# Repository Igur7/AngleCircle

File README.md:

# AngleCircle — czterowarstwowa płytka PCB do lokalizacji dźwięku

**AngleCircle** to projekt **okrągłej, czterowarstwowej płytki PCB**, opracowywanej w **KiCadzie** do systemu lokalizacji kierunku źródła dźwięku. System wykorzystuje **ESP32-S3** i **cztery cyfrowe mikrofony MEMS I²S**, rozmieszczone wokół płytki.

Celem projektu jest integracja elektroniki, zasilania i czujników w jednym module oraz ograniczenie problemów z połączeniami przewodowymi, które występowały na etapie prototypowania.

## Założenia projektowe

- Okrągła geometria płytki dostosowana do układu czterech mikrofonów.
- **Cztery warstwy miedzi** umożliwiające rozdzielenie sygnałów, zasilania oraz pól masy.
- Projektowanie ciągłych ścieżek prądu powrotnego i odpowiedniego połączenia obszarów GND za pomocą przelotek.
- Prowadzenie linii **I²S** (BCLK, WS/LRCLK i DATA) z uwzględnieniem integralności sygnałów i geometrii połączeń.
- Integracja z mikrokontrolerem **ESP32-S3** oraz elementami elektroniki pomocniczej.
- Przygotowanie schematu i layoutu PCB w **KiCadzie**.

## Architektura mikrofonów

Cztery mikrofony tworzą dwie pary pomiarowe, używane do estymacji opóźnienia nadejścia dźwięku (**TDOA**):

```text
         GÓRA

  MIC 1          MIC 2
 (lewy górny)  (prawy górny)
       \        /
        \      /
         \    /
          \  /
           \/
           /\
          /  \
         /    \
        /      \
       /        \
  MIC 3          MIC 4
 (lewy dolny) (prawy dolny)

         DÓŁ

 I²S1: MIC 1 + MIC 4
 I²S0: MIC 2 + MIC 3
```

Przyjęta w firmware koncepcja pomiaru łączy mikrofony w **dwie przekątne**. Każda przekątna jest obsługiwana przez oddzielny kontroler I²S, aby zapewnić synchronizację wewnątrz pary pomiarowej.

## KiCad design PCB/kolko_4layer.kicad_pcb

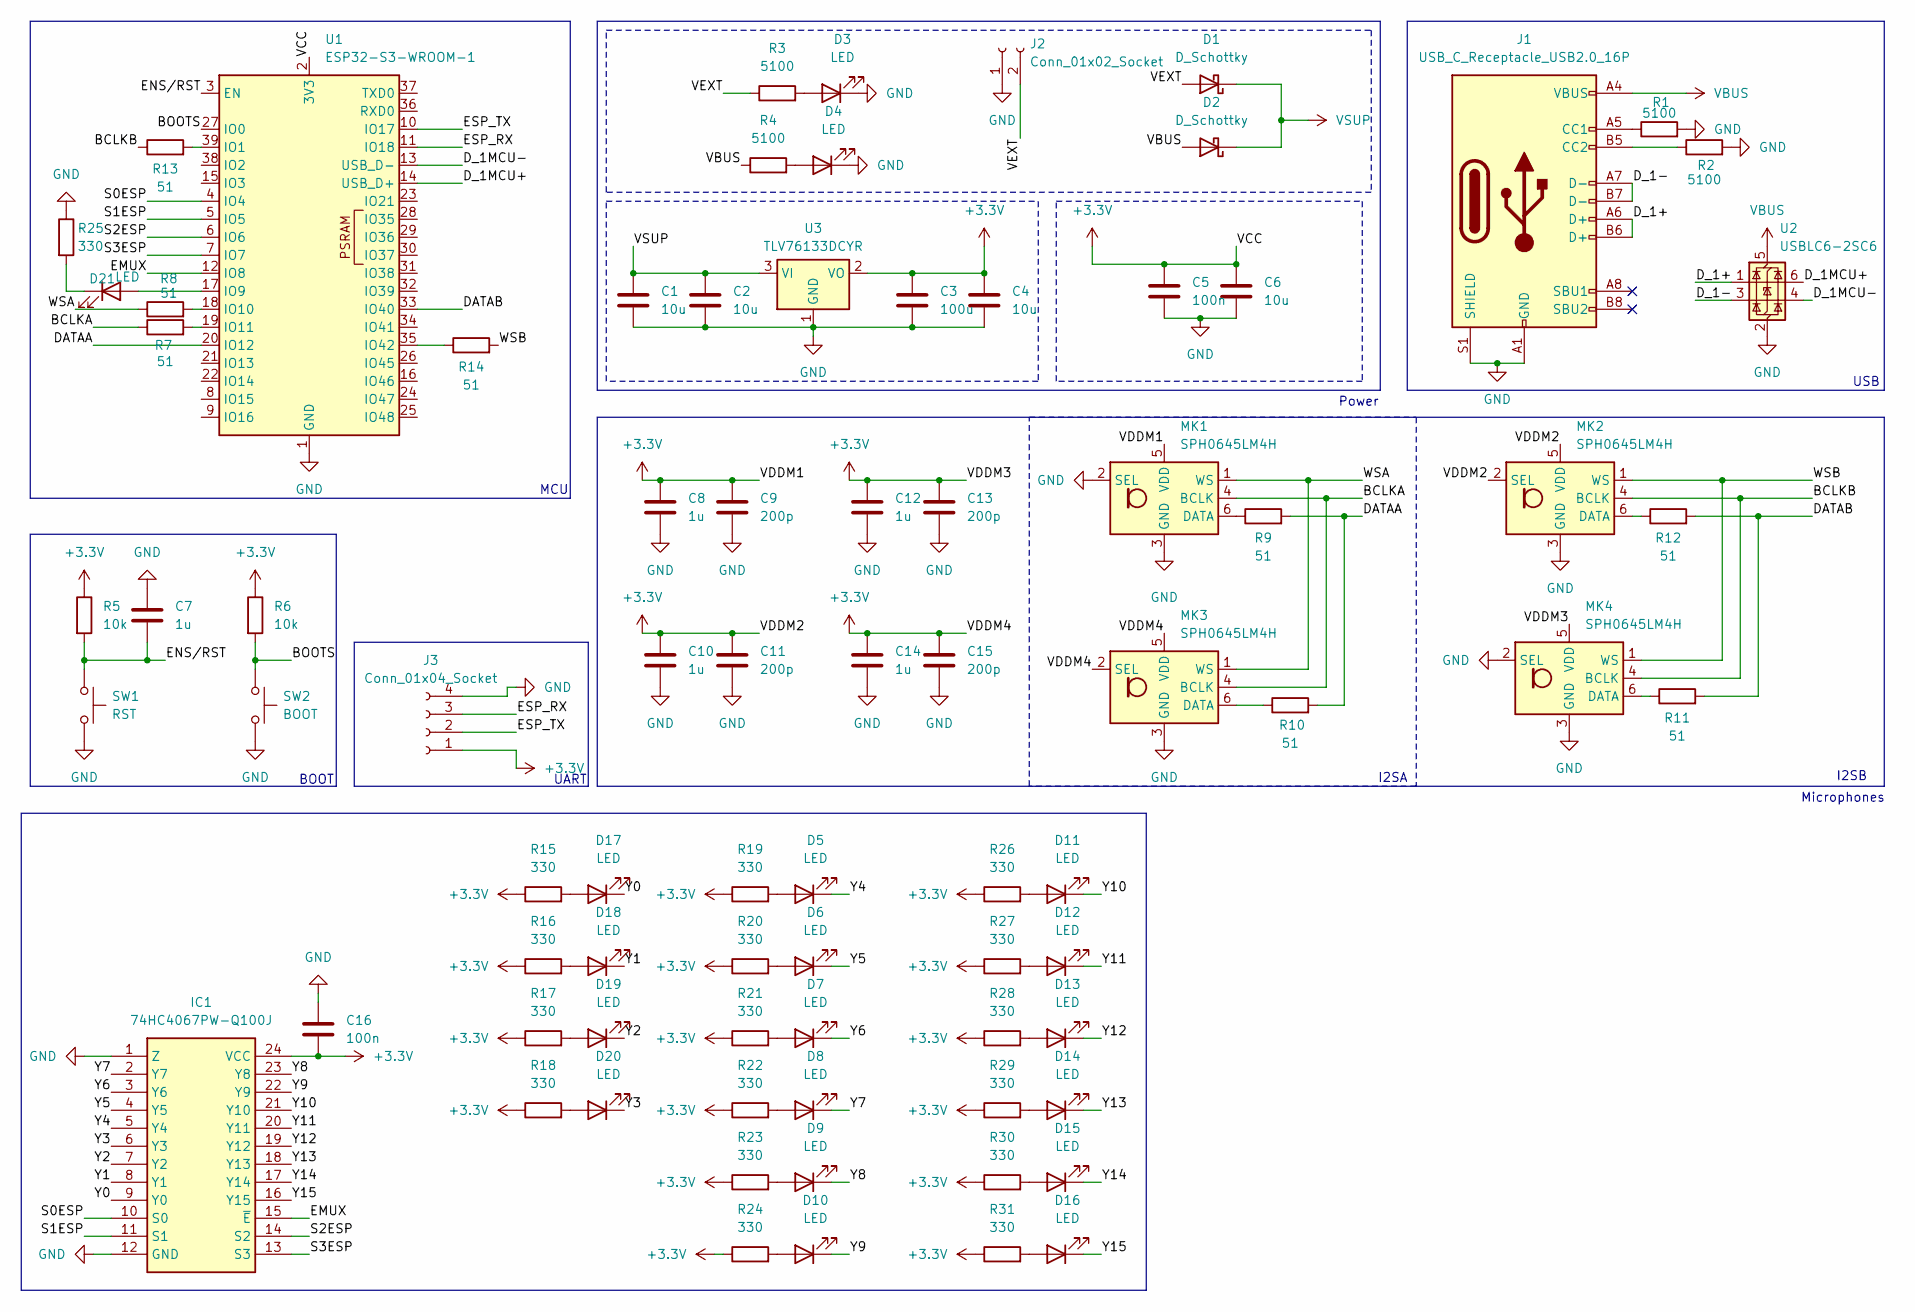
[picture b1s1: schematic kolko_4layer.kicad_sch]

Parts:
C1, C2, C4, C6: 10u; C_0805_2012Metric
C3: 100u; C_0805_2012Metric
C5, C16: 100n; C_0805_2012Metric
C7, C8, C10, C12, C14: 1u; C_0805_2012Metric
C9, C11, C13, C15: 200p; C_0805_2012Metric
D1, D2: D_Schottky; D_SMB
D3, D4, D5, D6, D7, D8, D9, D10, D11, D12, D13, D14, D15, D16, D17, D18, D19, D20, D21: LED; LED_0805_2012Metric_Pad1.15x1.40mm_HandSolder
IC1: 74HC4067PW-Q100J; TSSOP-24_4.4x7.8mm_P0.65mm; Mouser Part Number 771-74HC4067PW-Q100J
J1: USB_C_Receptacle_USB2.0_16P; USB_C_Receptacle_GCT_USB4105-xx-A_16P_TopMnt_Horizontal
J2: Conn_01x02_Socket; TerminalBlock_MaiXu_MX126-5.0-02P_1x02_P5.00mm
J3: Conn_01x04_Socket; Molex_PicoBlade_53047-0410_1x04_P1.25mm_Vertical
MK1, MK2, MK3, MK4: SPH0645LM4H; Knowles_SPH0645LM4H-6_3.5x2.65mm
R1, R2, R3, R4: 5100; R_0805_2012Metric
R5, R6: 10k; R_0805_2012Metric
R7, R8, R9, R10, R11, R12, R13, R14: 51; R_0805_2012Metric
R15, R16, R17, R18, R19, R20, R21, R22, R23, R24, R25, R26, R27, R28, R29, R30, R31: 330; R_0805_2012Metric
SW1: RST; SW_Push_1P1T-SH_NO_CK_KMR2xxG
SW2: BOOT; SW_Push_1P1T-SH_NO_CK_KMR2xxG
U1: ESP32-S3-WROOM-1; ESP32S3WROOM1UN16R8
U2: USBLC6-2SC6; SOT-23-6
U3: TLV76133DCYR; SOT-223-3_TabPin2

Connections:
+3.3V: C3.1, C4.1, C5.1, C6.1, C8.1, C9.1, C10.1, C11.1, C12.1, C13.1, C14.1, C15.1, C16.2, IC1.24 (VCC), J3.1, MK1.5 (VDD), MK2.2 (SEL), MK2.5 (VDD), MK3.2 (SEL), MK3.5 (VDD), MK4.5 (VDD), R5.1, R6.1, R15.1, R16.1, R17.1, R18.1, R19.1, R20.1, R21.1, R22.1, R23.1, R24.1, R26.1, R27.1, R28.1, R29.1, R30.1, R31.1, U1.2 (3V3), U3.2 (VO)
/BCLKA: MK1.4 (BCLK), MK3.4 (BCLK), R7.1
/BCLKB: MK2.4 (BCLK), MK4.4 (BCLK), R13.1
/BOOTS: R6.2, SW2.1, U1.27 (IO0)
/DATAA: R9.2, R10.2, U1.20 (IO12)
/DATAB: R11.2, R12.2, U1.33 (IO40)
/D_1+: J1.A6 (D+), J1.B6 (D+), U2.1 (I/O1)
/D_1-: J1.A7 (D-), J1.B7 (D-), U2.3 (I/O2)
/D_1MCU+: U1.14 (USB_D+), U2.6 (I/O1)
/D_1MCU-: U1.13 (USB_D-), U2.4 (I/O2)
/EMUX: IC1.15 (~E), U1.12 (IO8)
/ENS/RST: C7.2, R5.2, SW1.1, U1.3 (EN)
/ESP_RX: J3.3, U1.11 (IO18)
/ESP_TX: J3.2, U1.10 (IO17)
/S0ESP: IC1.10 (S0), U1.4 (IO4)
/S1ESP: IC1.11 (S1), U1.5 (IO5)
/S2ESP: IC1.14 (S2), U1.6 (IO6)
/S3ESP: IC1.13 (S3), U1.7 (IO7)
/VEXT: D1.2 (A), J2.2, R3.1
/WSA: MK1.1 (WS), MK3.1 (WS), R8.1
/WSB: MK2.1 (WS), MK4.1 (WS), R14.2
/Y0: D17.1 (K), IC1.9 (Y0)
/Y1: D18.1 (K), IC1.8 (Y1)
/Y2: D19.1 (K), IC1.7 (Y2)
/Y3: D20.1 (K), IC1.6 (Y3)
/Y4: D5.1 (K), IC1.5 (Y4)
/Y5: D6.1 (K), IC1.4 (Y5)
/Y6: D7.1 (K), IC1.3 (Y6)
/Y7: D8.1 (K), IC1.2 (Y7)
/Y8: D9.1 (K), IC1.23 (Y8)
/Y9: D10.1 (K), IC1.22 (Y9)
/Y10: D11.1 (K), IC1.21 (Y10)
/Y11: D12.1 (K), IC1.20 (Y11)
/Y12: D13.1 (K), IC1.19 (Y12)
/Y13: D14.1 (K), IC1.18 (Y13)
/Y14: D15.1 (K), IC1.17 (Y14)
/Y15: D16.1 (K), IC1.16 (Y15)
GND: C1.2, C2.2, C3.2, C4.2, C5.2, C6.2, C7.1, C8.2, C9.2, C10.2, C11.2, C12.2, C13.2, C14.2, C15.2, C16.1, D3.1 (K), D4.1 (K), IC1.1 (Z), IC1.12 (GND), J1.A1 (GND), J1.A12 (GND), J1.B1 (GND), J1.B12 (GND), J1.S1 (SHIELD), J2.1, J3.4, MK1.2 (SEL), MK1.3 (GND), MK2.3 (GND), MK3.3 (GND), MK4.2 (SEL), MK4.3 (GND), R1.2, R2.2, R25.1, SW1.2, SW2.2, U1.1 (GND), U1.40 (GND), U1.41 (GND), U2.2 (GND), U3.1 (GND)
unnamed: D3.2 (A), R3.2
unnamed: D4.2 (A), R4.2
unnamed: D5.2 (A), R19.2
unnamed: D6.2 (A), R20.2
unnamed: D7.2 (A), R21.2
unnamed: D8.2 (A), R22.2
unnamed: D9.2 (A), R23.2
unnamed: D10.2 (A), R24.2
unnamed: D11.2 (A), R26.2
unnamed: D12.2 (A), R27.2
unnamed: D13.2 (A), R28.2
unnamed: D14.2 (A), R29.2
unnamed: D15.2 (A), R30.2
unnamed: D16.2 (A), R31.2
unnamed: D17.2 (A), R15.2
unnamed: D18.2 (A), R16.2
unnamed: D19.2 (A), R17.2
unnamed: D20.2 (A), R18.2
unnamed: D21.2 (A), U1.17 (IO9)
unnamed: D21.1 (K), R25.2
unnamed: J1.A5 (CC1), R1.1
unnamed: J1.B5 (CC2), R2.1
unnamed: MK1.6 (DATA), R9.1
unnamed: MK2.6 (DATA), R12.1
unnamed: MK3.6 (DATA), R10.1
unnamed: MK4.6 (DATA), R11.1
unnamed: R13.2, U1.39 (IO1)
unnamed: R8.2, U1.18 (IO10)
unnamed: R7.2, U1.19 (IO11)
unnamed: R14.1, U1.35 (IO42)
VBUS: D2.2 (A), J1.A4 (VBUS), J1.A9 (VBUS), J1.B4 (VBUS), J1.B9 (VBUS), R4.1, U2.5 (VBUS)
VSUP: C1.1, C2.1, D1.1 (K), D2.1 (K), U3.3 (VI)

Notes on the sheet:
BOOT
Power
MCU
Microphones
USB
I2SB
I2SA
UART

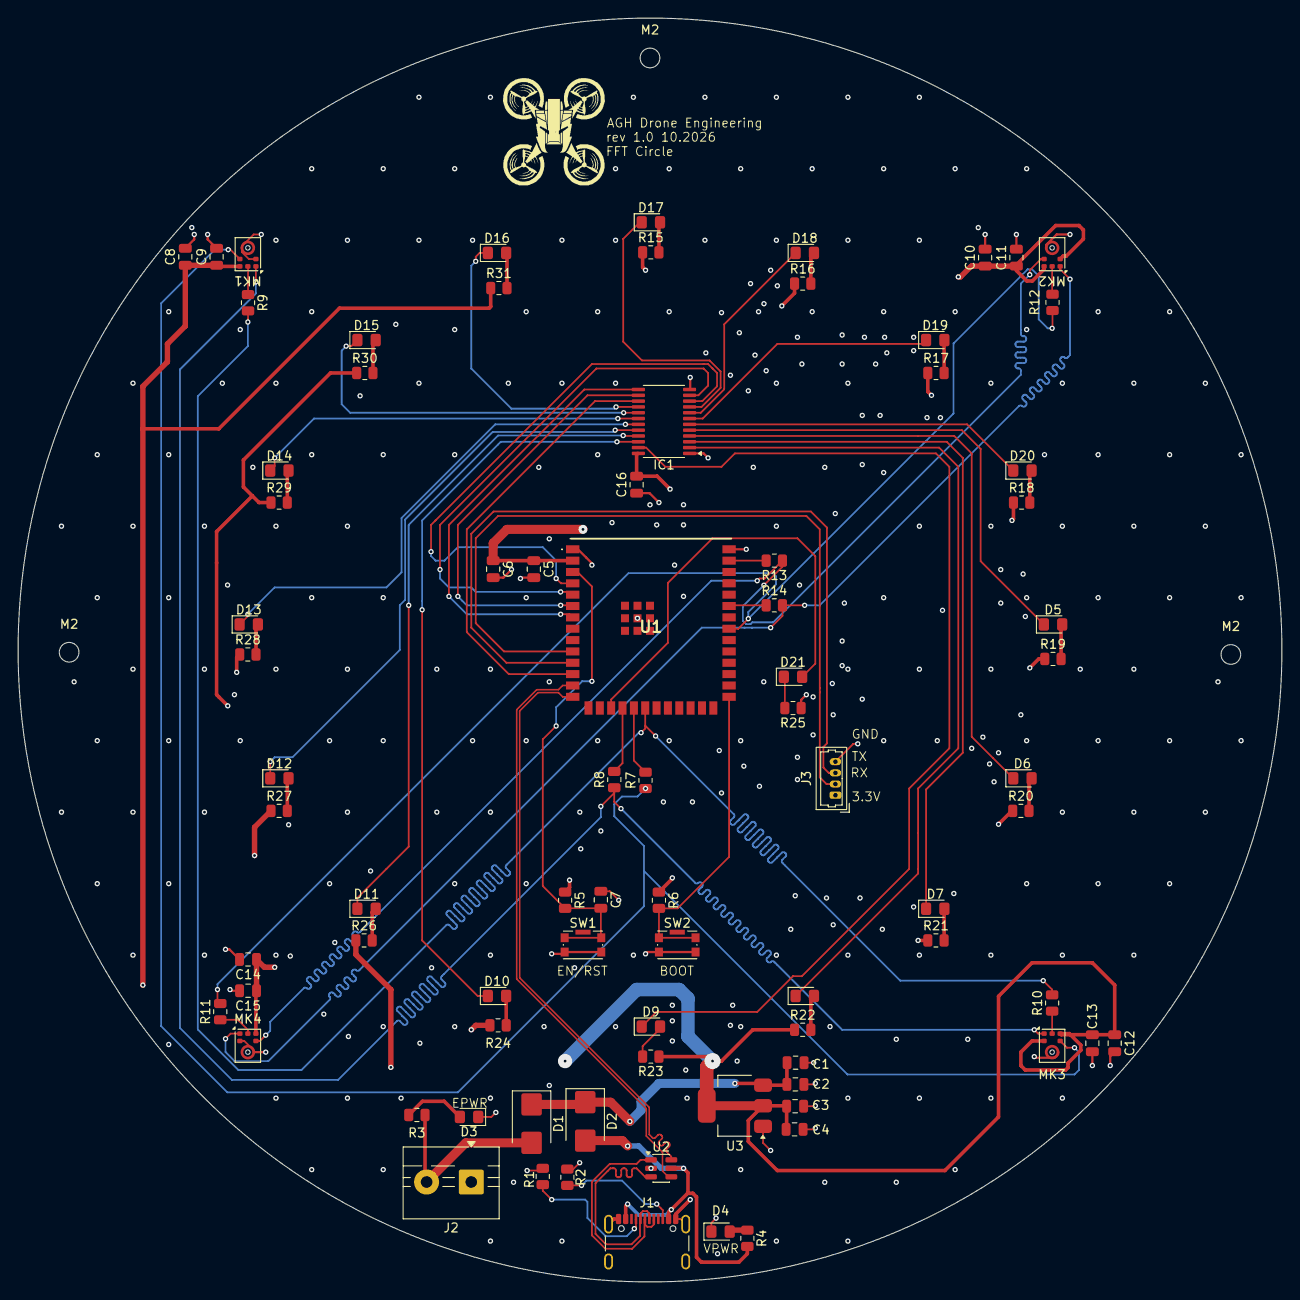
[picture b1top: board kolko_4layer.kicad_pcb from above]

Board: 4 copper layers, 141.4 x 141.4 mm, 84 parts (0 on the bottom side), 70 nets.

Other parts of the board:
M2, M2#2, M2#3: MountingHole_2.2mm_M2

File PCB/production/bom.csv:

Designator,Footprint,Quantity,Value,LCSC Part #
"C1, C2, C4, C6",0805,4,10u,
"C10, C12, C14, C7, C8",0805,5,1u,
"C11, C13, C15, C9",0805,4,200p,
"C16, C5",0805,2,100n,
C3,0805,1,100u,
"D1, D2",D_SMB,2,D_Schottky,
"D10, D11, D12, D13, D14, D15, D16, D17, D18, D19, D20, D21, D3, D4, D5, D6, D7, D8, D9",0805,19,LED,
IC1,TSSOP-24_4.4x7.8mm_P0.65mm,1,74HC4067PW-Q100J,
J1,USB_C_Receptacle_GCT_USB4105-xx-A_16P_TopMnt_Horizontal,1,USB_C_Receptacle_USB2.0_16P,
J2,TerminalBlock_MaiXu_MX126-5.0-02P_1x02_P5.00mm,1,Conn_01x02_Socket,
J3,Molex_PicoBlade_53047-0410_1x04_P1.25mm_Vertical,1,Conn_01x04_Socket,
"MK1, MK2, MK3, MK4",Knowles_SPH0645LM4H-6_3.5x2.65mm,4,SPH0645LM4H,
"R1, R2, R3, R4",0805,4,5100,
"R10, R11, R12, R13, R14, R7, R8, R9",0805,8,51,
"R15, R16, R17, R18, R19, R20, R21, R22, R23, R24, R25, R26, R27, R28, R29, R30, R31",0805,17,330,
"R5, R6",0805,2,10k,
SW1,SW_Push_1P1T-SH_NO_CK_KMR2xxG,1,RST,
SW2,SW_Push_1P1T-SH_NO_CK_KMR2xxG,1,BOOT,
U1,ESP32S3WROOM1UN16R8,1,ESP32-S3-WROOM-1,
U2,SOT-23-6,1,USBLC6-2SC6,
U3,SOT-223-3_TabPin2,1,AMS1117-3.3,
